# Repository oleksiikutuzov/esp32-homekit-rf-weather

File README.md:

# esp32-homekit-rf-weather

The software is based on [HomeSpan](https://github.com/HomeSpan/HomeSpan) and [RTL_433_ESP](https://github.com/NorthernMan54/rtl_433_ESP) libraries.

> **Warning**
> Don't expect any warranties. I am just a hobbyist, not a professional. It works for me, but you take your own risk using it. I am not liable for any damage to your devices.

## Hardware requirements

1. [Custom PCB](https://github.com/oleksiikutuzov/esp32-homekit-rf-weather/tree/main/PCB) (BOM inside) from this project 
   
   or 
   
   any ESP32 Dev board e.g. [ESP32-DevKitC V4 board](https://docs.espressif.com/projects/esp-idf/en/latest/esp32/hw-reference/esp32/get-started-devkitc.html)
2. [E07-M1101D](https://manuals.plus/ebyte/e07-m1101d-sma-cc1101-433mhz-dip-wireless-module-manual#axzz7j0rVAbnv) 433 MHz Wireless module 

## Pinout

### Wireless module pins

If you are using a dev board, you will need to connect the wireless module to some specific pins of ESP32.

```
ESP32          Module
---------------------
GPIO18         SCK
GPIO19         MISO
GPIO23         MOSI
GPIO5          CS
GPIO22         GDO0
GPIO4          GDO2
```

### LEDs and control button pins

If you are using a dev board, you can utilize any pins you want or not use them at all. There is a control button to be able to reset the device, WIFI or HomeKit configuration. The status pin shows the current state of the device. More info on the status LED and control button is in [HomeSpan User](https://github.com/HomeSpan/HomeSpan/blob/master/docs/UserGuide.md) Guide](https://github.com/HomeSpan/HomeSpan/blob/master/docs/UserGuide.md). Three additional LEDs are blinking on the received signal on any of the channels. To redefine the pins for the dev board edit the following in the sketch:
```C++
#ifdef DEV_BOARD
	#define LED_CH1    13
	#define LED_CH2    21
	#define LED_CH3    17
	#define LED_STATUS 16
	#define BUTTON_PIN 15
```

## How to setup and install

1. Install [PlatformIO Core](https://platformio.org/install/cli) and [VSCode Plugin](https://docs.platformio.org/page/ide/vscode.html) (setup I am using and tested the instructions on) or [PlatformIO IDE](https://platformio.org/install/ide) with built-in Core.
2. Clone this repository
In the `platformio.ini` file set the default environment to `esp32_dev_board` or `esp32_custom_pcb` depending on the board you are using.
   ```
   [platformio]
   default_envs = esp32_custom_pcb
   ```
4. Build the firmware with a dedicated button in the PlatformIO extension or with the command 
   ```
   pio run
   ```
5. Upload the firmware with a dedicated button in the PlatformIO extension or with the command 
   ```
   pio run --target upload
   ```
6. You can monitor the serial output to check everything is working as intended with a dedicated button in the PlatformIO extension or with the command
   ```
   pio run --target monitor
   ```

## Custom Hardware

Custom PCB is designed for the project. Currently for regular ESP32 boards.

## Connect to HomeKit

1. Plug your LED Controller to power
2. The access point should start automatically. 
> **Note**
> Later you can manually enter configuration mode (More on [HomeSpan User Guide](https://github.com/HomeSpan/HomeSpan/blob/master/docs/UserGuide.md))
3. Go to WiFi settings on your iPhone/iPad and connect to the "HomeSpan-Setup" WiFi network
4. You will choose your WiFi network and set the setup code for the accessory
5. Go to your Home app and select "Add Accessory"
6. Select "More Options" and you should see your RF Weather Bridge there
## Settings and controls

When adding to HomeKit it will add the unsupported device called **RF Weather Bridge Settings** with device settings (3rd party apps like Eve support this and can be used for configuration). Available custom characteristics:
1. Toggle whether to blink the LEDs on receive
2. Showing the IP address the device is connected to
Set the number of channels, on which you want to receive (created an accessory for each channel). Can be set as 1 to 3
4. Toggle to reboot the device (to reload the device if you change the number of channels)

The device will throw a Status Fault in Eve app if there are no sensor updates for 5 minutes. 

Characteristics values are saved to NVS, so they will be restored if the device loses power. 

The web server update was implemented. You can flash binary at `http://[DEVICE IP]/update`.
There is a reboot link. Opening `http://[DEVICE IP]/reboot` will force the device to reboot. 

The device can also be controlled by the button on the board. More on [HomeSpan User Guide](https://github.com/HomeSpan/HomeSpan/blob/master/docs/UserGuide.md)

## TODO
### PCB:
- [ ] Add a USB-to-Serial converter to the board
- [ ] Make more space for flashing pin headers

## References and sources

- @HomeSpan for ESP32 HomeKit firmware [GitHub link](https://github.com/HomeSpan/HomeSpan)
- @NorthernMan54 for rtl_433_ESP library [GitHub link](https://github.com/NorthernMan54/rtl_433_ESP)

Although already forbidden by the sources and subsequent licensing, it is not allowed to use or distribute this software for commercial purposes.<br/><br/>

###### HomeKit Accessory Protocol (HAP) is Apple’s proprietary protocol that enables third-party accessories in the home (e.g., lights, thermostats and door locks) and Apple products to communicate with each other. HAP supports two transports, IP and Bluetooth LE. The information provided in the HomeKit Accessory Protocol Specification (Non-Commercial Version) describes how to implement HAP in an accessory that you create for non-commercial use and that will not be distributed or sold.

###### The HomeKit Accessory Protocol Specification (Non-Commercial Version) can be downloaded from the [HomeKit Apple Developer page.](https://developer.apple.com/homekit/)

###### Copyright © 2019 Apple Inc. All rights reserved.

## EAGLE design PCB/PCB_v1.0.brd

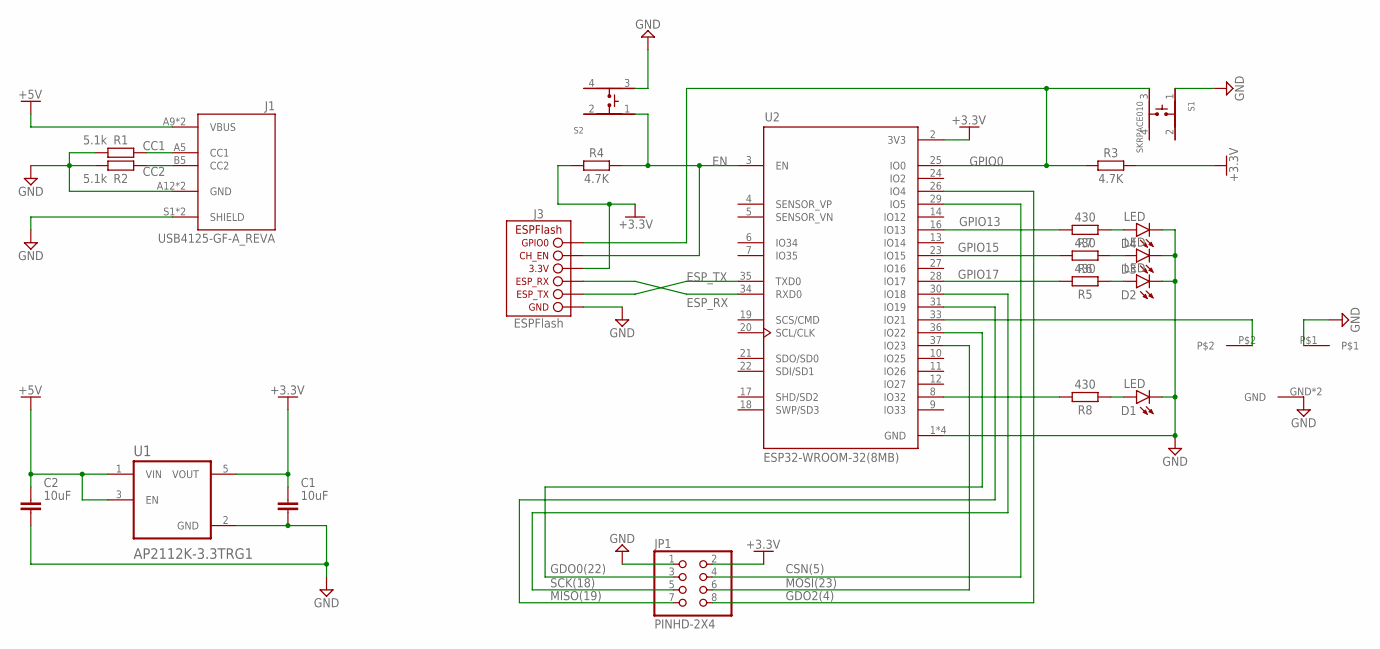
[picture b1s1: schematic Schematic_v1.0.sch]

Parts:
C1, C2: 10uF; CAPC1608X85
D1, D2, D3, D4: LED; LEDC1608X80N_FLAT-R
J1: USB4125-GF-A_REVA; CUI_UJC-VP-3-SMT-TR
J3: ESPFLASH-2X3-2.54-PLAIN; 2X3-2.54-PLAIN
JP1: PINHD-2X4; 2X04
R1, R2: 5.1k; RESC1608X60
R3, R4: 4.7K; RESC1608X60
R5, R6, R7, R8: 430; RESC1608X60
S1, S2: SKRPACE010; SW_SKRPACE010
U1: AP2112K-3.3TRG1; SOT95P285X140-5N
U2: ESP32-WROOM-32(8MB); MODULE_ESP32-WROOM-32(8MB)
U$1: MOMENTARY-SWITCH; SWITCH-MOMENTARY

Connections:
+3.3V: C1.1, J3.2 (3.3V), JP1.2, R3.2, R4.1, U1.5 (VOUT), U2.2 (3V3)
+5V: C2.1, J1.A9 (VBUS), J1.B9 (VBUS), U1.1 (VIN), U1.3 (EN)
CC1: J1.A5 (CC1), R1.1
CC2: J1.B5 (CC2), R2.1
CSN(5): JP1.4, U2.29 (IO5)
EN: J3.1 (CH_EN), R4.2, S2.1, U2.3 (EN)
ESP_RX: J3.5 (ESP_RX), U2.34 (RXD0)
ESP_TX: J3.3 (ESP_TX), U2.35 (TXD0)
GDO0(22): JP1.3, U2.36 (IO22)
GDO2(4): JP1.8, U2.26 (IO4)
GND: C1.2, C2.2, D1.C, D2.C, D3.C, D4.C, J1.A12 (GND), J1.B12 (GND), J1.S1 (SHIELD), J1.S2 (SHIELD), J3.4 (GND), JP1.1, R1.2, R2.2, S1.1, S2.3, U1.2 (GND), U2.1 (GND), U2.15 (GND), U2.38 (GND), U2.39 (GND), U$1.GND, U$1.GND_2 (GND), U$1.P$1
GPIO0: J3.6 (GPIO0), R3.1, S1.3, U2.25 (IO0)
GPIO13: R7.2, U2.16 (IO13)
GPIO15: R6.2, U2.23 (IO15)
GPIO17: R5.2, U2.28 (IO17)
MISO(19): JP1.7, U2.31 (IO19)
MOSI(23): JP1.6, U2.37 (IO23)
unnamed: D1.A, R8.1
unnamed: R8.2, U2.8 (IO32)
unnamed: D2.A, R5.1
unnamed: U2.33 (IO21), U$1.P$2
unnamed: D3.A, R6.1
unnamed: D4.A, R7.1
SCK(18): JP1.5, U2.30 (IO18)

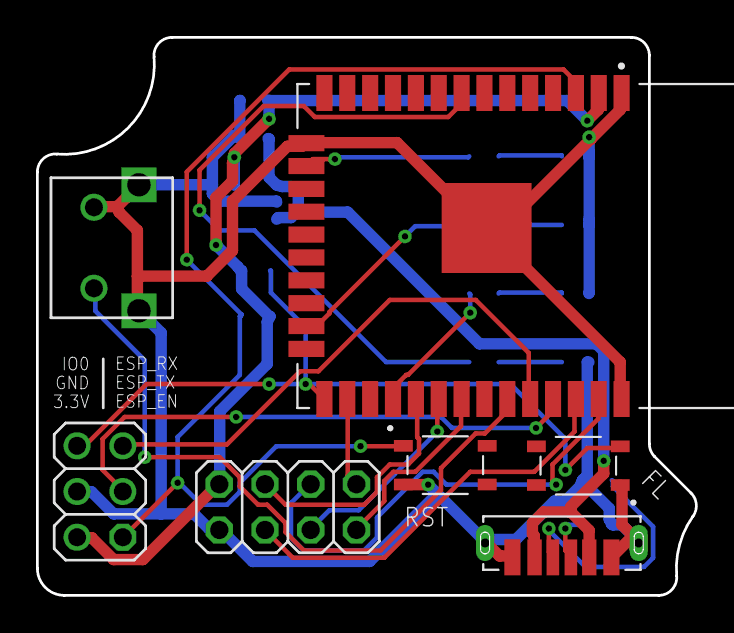
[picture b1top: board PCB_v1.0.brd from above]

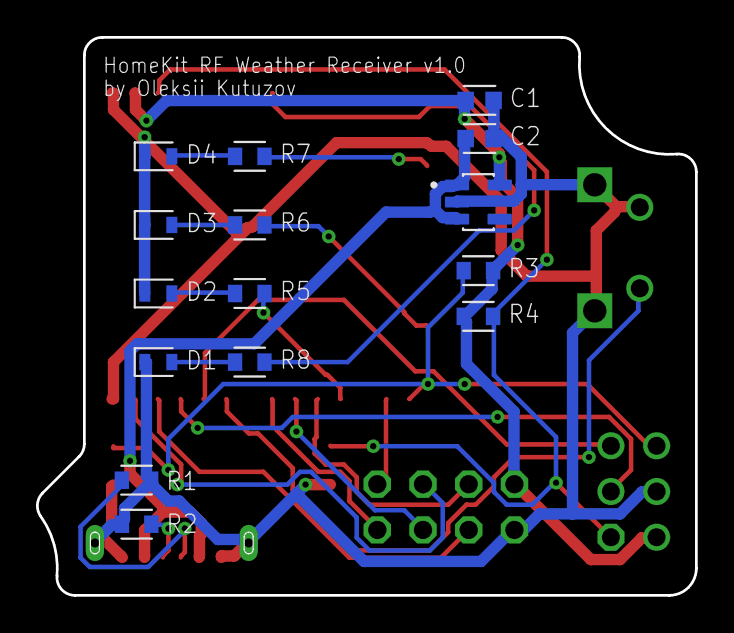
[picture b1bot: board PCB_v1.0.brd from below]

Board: 2 copper layers, 36.6 x 31.0 mm, 22 parts (15 on the bottom side), 24 nets.

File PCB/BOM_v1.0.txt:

Partlist exported from /var/folders/tq/b2m_bkf11ld61j4hqq2g93cr0000gn/T/Neutron/ElectronFileOutput/48587/sch-562322ec-a9bd-47c2-8610-2d14c827d28f/Schematic v1.0 v14.sch at 28.10.22 16:01

Part Value                   Device                   Package                    Description                                                                 
C1   10uF                    C_CHIP-0603(1608-METRIC) CAPC1608X85                Capacitor - Generic                                                         
C2   10uF                    C_CHIP-0603(1608-METRIC) CAPC1608X85                Capacitor - Generic                                                         
D1   LED                     CHIP-FLAT-R_0603-0.80MM  LEDC1608X80N_FLAT-R                                                                                    
D2   LED                     CHIP-FLAT-R_0603-0.80MM  LEDC1608X80N_FLAT-R                                                                                    
D3   LED                     CHIP-FLAT-R_0603-0.80MM  LEDC1608X80N_FLAT-R                                                                                    
D4   LED                     CHIP-FLAT-R_0603-0.80MM  LEDC1608X80N_FLAT-R                                                                                    
J1   USB4125-GF-A_REVA       UJC-VP-3-SMT-TR          CUI_UJC-VP-3-SMT-TR        USB Receptacle                                                              
J3   ESPFLASH-2X3-2.54-PLAIN ESPFLASH-2X3-2.54-PLAIN  2X3-2.54-PLAIN             ESPFlash                                                                    
JP1  PINHD-2X4               PINHD-2X4                2X04                       PIN HEADER                                                                  
R1   5.1k                    R_CHIP-0603(1608-METRIC) RESC1608X60                Resistor Fixed - Generic                                                    
R2   5.1k                    R_CHIP-0603(1608-METRIC) RESC1608X60                Resistor Fixed - Generic                                                    
R3   4.7K                    R_CHIP-0603(1608-METRIC) RESC1608X60                Resistor Fixed - Generic                                                    
R4   4.7K                    R_CHIP-0603(1608-METRIC) RESC1608X60                Resistor Fixed - Generic                                                    
R5   430                     R_CHIP-0603(1608-METRIC) RESC1608X60                Resistor Fixed - Generic                                                    
R6   430                     R_CHIP-0603(1608-METRIC) RESC1608X60                Resistor Fixed - Generic                                                    
R7   430                     R_CHIP-0603(1608-METRIC) RESC1608X60                Resistor Fixed - Generic                                                    
R8   430                     R_CHIP-0603(1608-METRIC) RESC1608X60                Resistor Fixed - Generic                                                    
S1   SKRPACE010              SKRPACE010               SW_SKRPACE010              Switch Tactile N.O. SPST Button J-Bend 0.05A 16VDC 2.55N SMD Automotive T/R 
S2   SKRPACE010              SKRPACE010               SW_SKRPACE010              Switch Tactile N.O. SPST Button J-Bend 0.05A 16VDC 2.55N SMD Automotive T/R 
U$1  MOMENTARY-SWITCH        MOMENTARY-SWITCH         SWITCH-MOMENTARY                                                                                       
U1   AP2112K-3.3TRG1         AP2112K-3.3TRG1          SOT95P285X140-5N           AP2112 Series 0.6 A 3.3 V Fixed Output SMT LDO Linear Regulator - SOT23-5   
U2   ESP32-WROOM-32(8MB)     ESP32-WROOM-32(8MB)      MODULE_ESP32-WROOM-32(8MB) WIFI MODULE 64 MBITS SPI FLASH

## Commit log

2022-09-07 Working program
2022-09-07 Add build action
2022-09-08 Add second sensor
2022-09-08 Fix names
2022-09-08 Different build configs with 1 to 3 channels
2022-09-08 Fix binaries link
2022-09-08 Set default env
2022-09-08 Test saving artifact
2022-09-08 Update export_bin.yml
    Checkout with PAT
2022-09-08 Automated Binary Upload
2022-09-08 Update build script
2022-09-08 Edit export action
2022-09-08 Test update
2022-09-08 Create bin folder
2022-09-09 Apply formatting
2022-09-09 Fix update url
2022-09-09 Fix channels enumeration for particular sensor
2022-09-10 Add battery status characteristic
2022-09-12 Change serial output to LOG1 macro
2022-09-15 Add LED blinks on receive
2022-09-15 Adjust names of devices
2022-09-15 Change upload baud rate
2022-09-16 Sort out negative values (errors)
2022-09-16 Bump version
2022-10-02 Add characteristics for OTA, number of devices, IP
2022-10-02 Reorganize code, dynamic switch number of channels
2022-10-02 Upload hardware files
2022-10-02 Minor fixes
2022-10-02 Switch to custom Service for settings
2022-10-02 Add reboot functionality
2022-10-02 Include new single binary
2022-10-02 Remove binaries
2022-10-02 Fix to prometheus metrics export
2022-10-03 Add pin numbers for pcb
2022-10-03 Separate build for pcb
2022-10-03 Misc files update
2022-10-03 Add fault state
2022-10-26 Auto update off by default
2022-10-26 Adjust platformio config
2022-10-26 Remove settings file
2022-10-28 Increase time before Status Fault is triggered
2022-10-28 Remove Auto OTA
2022-10-28 Edit build action
2022-10-28 Adjust PIO config
2022-10-28 Update resources
2022-10-28 Add more images and adjust Readme
2022-10-28 Add BOM
2022-10-28 Remove some files
2022-10-28 Remove file
2022-10-28 Adjust config
2022-11-12 Compact serial output
2022-11-12 Fix formatting
2022-11-16 Move radio receive to service loop
2022-11-16 Add last received characteristic
2022-11-16 Bump RTL_433_ESP dependency
2022-11-23 Settings as device of the first sensor
